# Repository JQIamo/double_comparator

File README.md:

# double_comparator
Double comparator board for synchronizing mode-locked lasers
The design is finished and is currently being tested for performance.

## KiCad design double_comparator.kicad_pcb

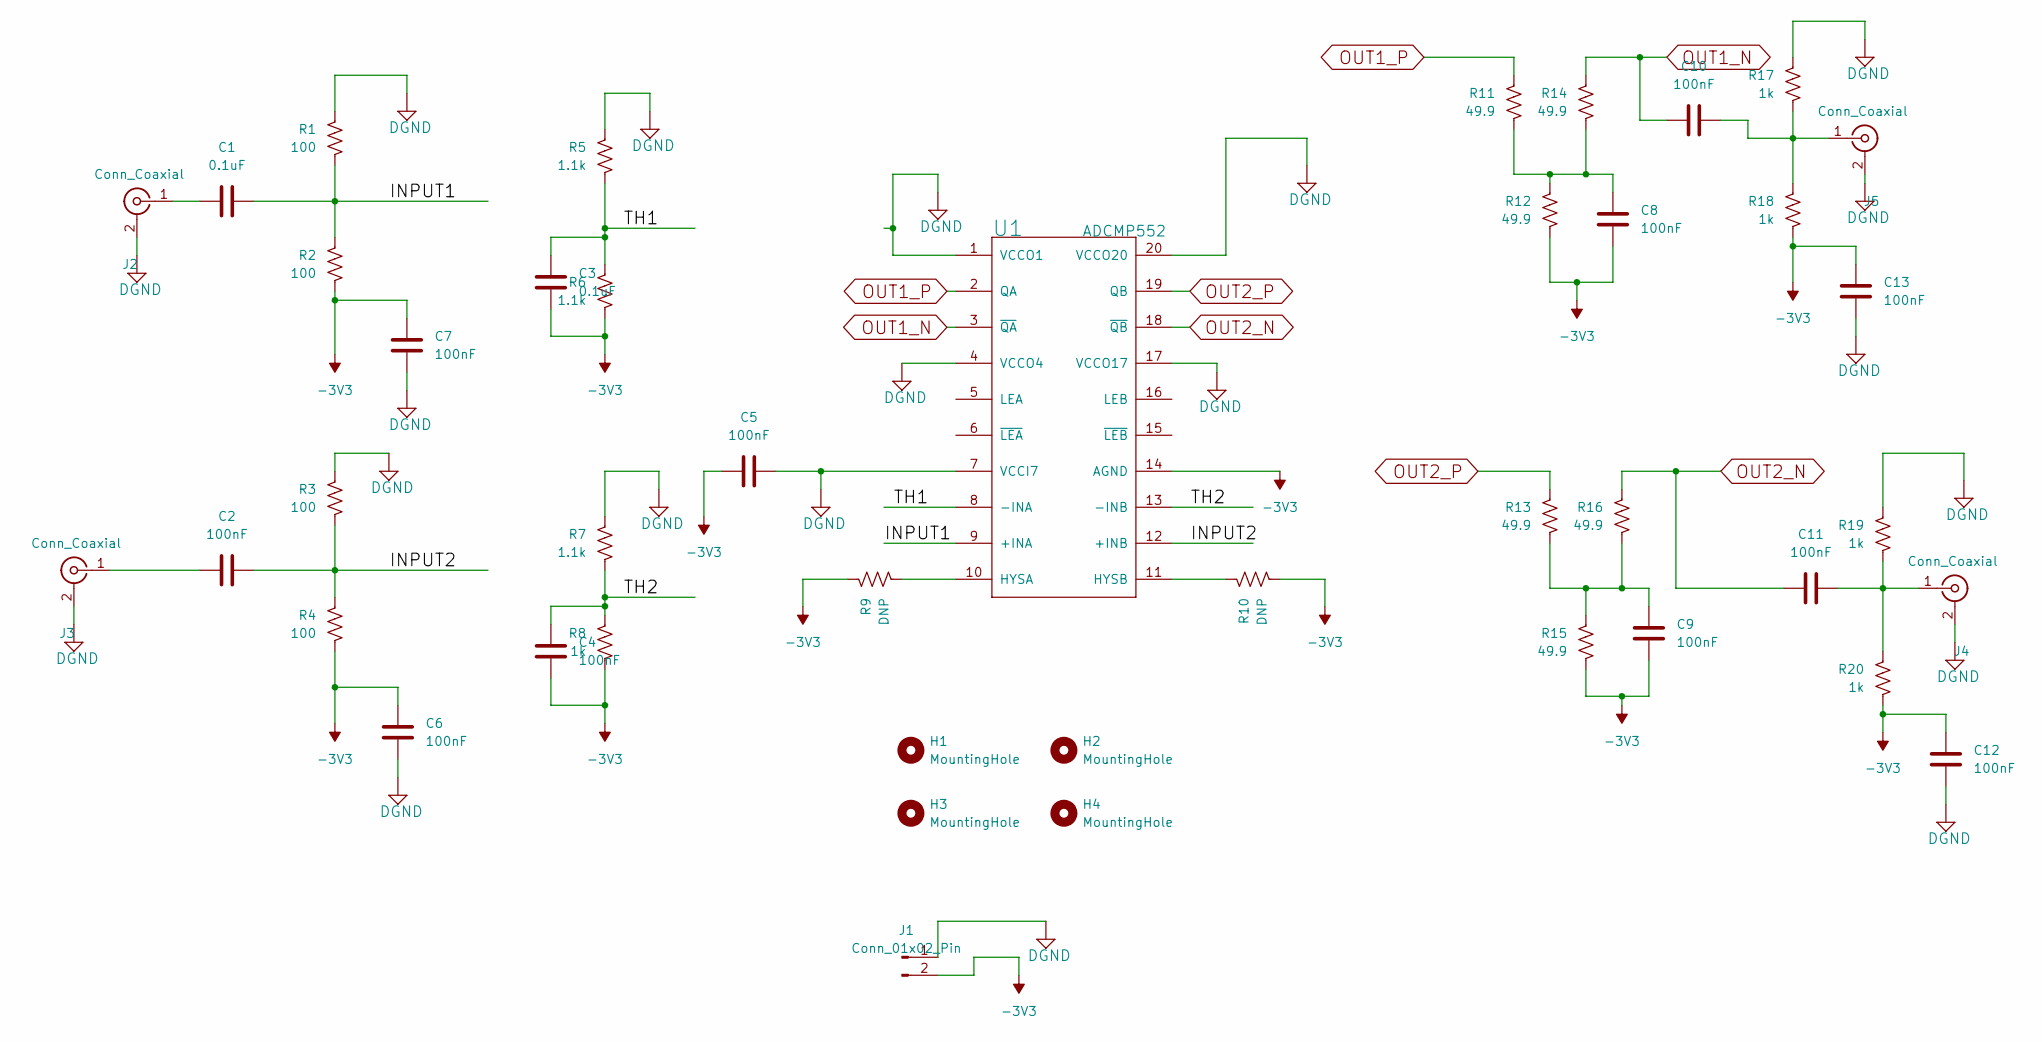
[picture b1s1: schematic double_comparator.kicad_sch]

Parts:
C1, C3: 0.1uF; C_0603_1608Metric
C2, C4, C5, C6, C7, C8, C9, C10, C11, C12, C13: 100nF; C_0603_1608Metric
H1, H2, H3, H4: MountingHole; MountingHole_3mm
J1: Conn_01x02_Pin; Molex_KK-254_AE-6410-02A_1x02_P2.54mm_Vertical
J2, J3, J4, J5: Conn_Coaxial; BNC_V-BITE_PCB_EDGE
R1, R2, R3, R4: 100; R_0603_1608Metric
R5, R6, R7: 1.1k; R_0603_1608Metric
R8, R17, R18, R19, R20: 1k; R_0603_1608Metric
R9, R10: DNP; R_0603_1608Metric
R11, R12, R13, R14, R15, R16: 49.9; R_0603_1608Metric
U1: ADCMP552; QSOP-20_3.9x8.7mm_P0.635mm

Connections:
-3V3: C3.1, C4.2, C5.1, C6.1, C7.1, C8.2, C9.2, C12.1, C13.1, J1.2, R2.2, R4.2, R6.2, R8.2, R9.1, R10.2, R12.2, R15.2, R18.2, R20.2, U1.14 (AGND)
/INPUT1: C1.2, R1.2, R2.1, U1.9 (+INA)
/INPUT2: C2.2, R3.2, R4.1, U1.12 (+INB)
/TH1: C3.2, R5.2, R6.1, U1.8 (-INA)
/TH2: C4.1, R7.2, R8.1, U1.13 (-INB)
DGND: C5.2, C6.2, C7.2, C12.2, C13.2, J1.1, J2.2 (Ext), J3.2 (Ext), J4.2 (Ext), J5.2 (Ext), R1.1, R3.1, R5.1, R7.1, R17.1, R19.1, U1.1 (VCCO1), U1.4 (VCCO4), U1.7 (VCCI7), U1.17 (VCCO17), U1.20 (VCCO20)
unnamed: C8.1, R11.2, R12.1, R14.2
unnamed: C9.1, R13.2, R15.1, R16.2
unnamed: C1.1, J2.1 (In)
unnamed: C2.1, J3.1 (In)
unnamed: C11.2, J4.1 (In), R19.2, R20.1
unnamed: C10.2, J5.1 (In), R17.2, R18.1
unnamed: R9.2, U1.10 (HYSA)
unnamed: R10.1, U1.11 (HYSB)
OUT1_N: C10.1, R14.1, U1.3 (~QA)
OUT1_P: R11.1, U1.2 (QA)
OUT2_N: C11.1, R16.1, U1.18 (~QB)
OUT2_P: R13.1, U1.19 (QB)

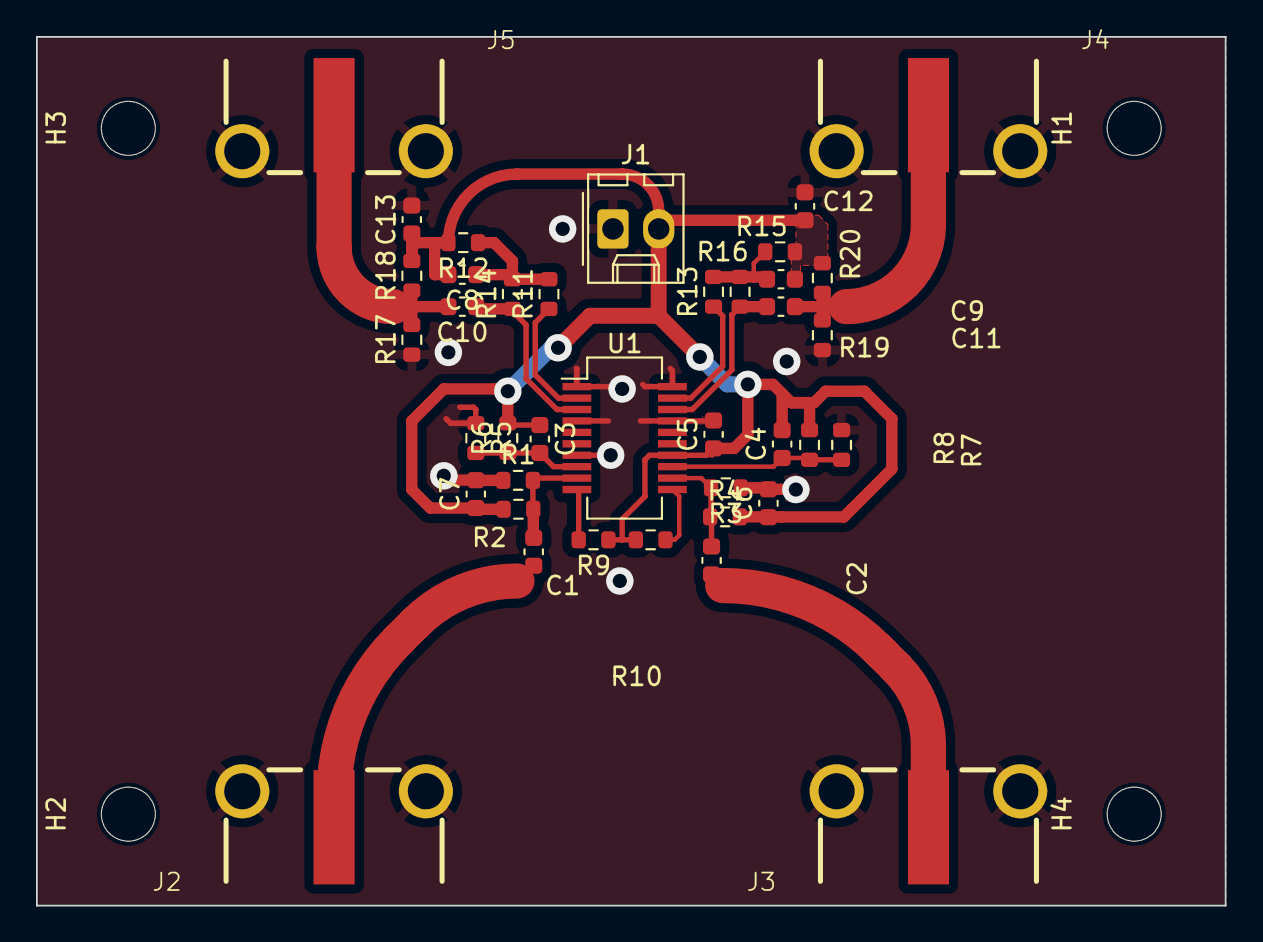
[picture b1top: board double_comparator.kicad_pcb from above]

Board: 2 copper layers, 66.0 x 48.3 mm, 43 parts (0 on the bottom side), 18 nets.

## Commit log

2023-05-15 Added Kicad files. This is not a final design
2023-05-15 Warning: design is incomplete
2023-05-15 typo
2023-06-09 updated design
2023-06-12 version ready to be printed
2023-07-11 current project state updated
